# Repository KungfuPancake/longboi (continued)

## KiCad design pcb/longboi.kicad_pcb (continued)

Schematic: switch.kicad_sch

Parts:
C63: 100nF; C_0603_1608Metric
D15: LED; LED_0603_1608Metric
J23: JST-XH; JST_XH_B3B-XH-A_1x03_P2.50mm_Vertical
R29: 100k; R_0603_1608Metric
R30: 100; R_0603_1608Metric
R79: 3.3k; R_0603_1608Metric

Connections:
+5V: D15.2 (A), J23.3, R29.1; also elsewhere on the board
/Endstops/Switch 16/SW: R30.2, R79.1; also elsewhere on the board
GND: C63.2, J23.2; also elsewhere on the board
unnamed: D15.1 (K), R79.2
unnamed: C63.1, J23.1, R29.2, R30.1

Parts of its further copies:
C64, C65, C66, C67, C68, C69, C70, C71, C72, C73, C74, C75, C76, C77, C78: 100nF; C_0603_1608Metric
D16, D17, D18, D19, D20, D21, D22, D23, D24, D25, D26, D27, D28, D29, D30: LED; LED_0603_1608Metric
J24, J25, J26, J27, J28, J29, J30, J31, J32, J33, J34, J35, J36, J37, J38: JST-XH; JST_XH_B3B-XH-A_1x03_P2.50mm_Vertical
R31, R33, R35, R37, R39, R41, R43, R45, R47, R49, R51, R53, R55, R57, R59: 100k; R_0603_1608Metric
R32, R34, R36, R38, R40, R42, R44, R46, R48, R50, R52, R54, R56, R58, R60: 100; R_0603_1608Metric
R80, R81, R82, R83, R84, R85, R86, R87, R88, R89, R90, R91, R92, R93, R94: 3.3k; R_0603_1608Metric

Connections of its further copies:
+5V: D16.2 (A), D17.2 (A), D18.2 (A), D19.2 (A), D20.2 (A), D21.2 (A), D22.2 (A), D23.2 (A), D24.2 (A), D25.2 (A), D26.2 (A), D27.2 (A), D28.2 (A), D29.2 (A), D30.2 (A), J24.3, J25.3, J26.3, J27.3, J28.3, J29.3, J30.3, J31.3, J32.3, J33.3, J34.3, J35.3, J36.3, J37.3, J38.3, R31.1, R33.1, R35.1, R37.1, R39.1, R41.1, R43.1, R45.1, R47.1, R49.1, R51.1, R53.1, R55.1, R57.1, R59.1; also elsewhere on the board
/Endstops/Switch 1/SW: R60.2, R94.1; also elsewhere on the board
/Endstops/Switch 2/SW: R56.2, R92.1; also elsewhere on the board
/Endstops/Switch 3/SW: R48.2, R88.1; also elsewhere on the board
/Endstops/Switch 4/SW: R52.2, R90.1; also elsewhere on the board
/Endstops/Switch 5/SW: R44.2, R86.1; also elsewhere on the board
/Endstops/Switch 6/SW: R40.2, R84.1; also elsewhere on the board
/Endstops/Switch 7/SW: R36.2, R82.1; also elsewhere on the board
/Endstops/Switch 8/SW: R32.2, R80.1; also elsewhere on the board
/Endstops/Switch 9/SW: R58.2, R93.1; also elsewhere on the board
/Endstops/Switch 10/SW: R54.2, R91.1; also elsewhere on the board
/Endstops/Switch 11/SW: R50.2, R89.1; also elsewhere on the board
/Endstops/Switch 12/SW: R46.2, R87.1; also elsewhere on the board
/Endstops/Switch 13/SW: R42.2, R85.1; also elsewhere on the board
/Endstops/Switch 14/SW: R38.2, R83.1; also elsewhere on the board
/Endstops/Switch 15/SW: R34.2, R81.1; also elsewhere on the board
GND: C64.2, C65.2, C66.2, C67.2, C68.2, C69.2, C70.2, C71.2, C72.2, C73.2, C74.2, C75.2, C76.2, C77.2, C78.2, J24.2, J25.2, J26.2, J27.2, J28.2, J29.2, J30.2, J31.2, J32.2, J33.2, J34.2, J35.2, J36.2, J37.2, J38.2; also elsewhere on the board
unnamed: D16.1 (K), R80.2
unnamed: D17.1 (K), R81.2
unnamed: D18.1 (K), R82.2
unnamed: D19.1 (K), R83.2
unnamed: D20.1 (K), R84.2
unnamed: D21.1 (K), R85.2
unnamed: D22.1 (K), R86.2
unnamed: D23.1 (K), R87.2
unnamed: D24.1 (K), R88.2
unnamed: D25.1 (K), R89.2
unnamed: D26.1 (K), R90.2
unnamed: D27.1 (K), R91.2
unnamed: D28.1 (K), R92.2
unnamed: D29.1 (K), R93.2
unnamed: D30.1 (K), R94.2
unnamed: C64.1, J24.1, R31.2, R32.1
unnamed: C65.1, J25.1, R33.2, R34.1
unnamed: C66.1, J26.1, R35.2, R36.1
unnamed: C67.1, J27.1, R37.2, R38.1
unnamed: C68.1, J28.1, R39.2, R40.1
unnamed: C69.1, J29.1, R41.2, R42.1
unnamed: C70.1, J30.1, R43.2, R44.1
unnamed: C71.1, J31.1, R45.2, R46.1
unnamed: C72.1, J32.1, R47.2, R48.1
unnamed: C73.1, J33.1, R49.2, R50.1
unnamed: C74.1, J34.1, R51.2, R52.1
unnamed: C75.1, J35.1, R53.2, R54.1
unnamed: C76.1, J36.1, R55.2, R56.1
unnamed: C77.1, J37.1, R57.2, R58.1
unnamed: C78.1, J38.1, R59.2, R60.1

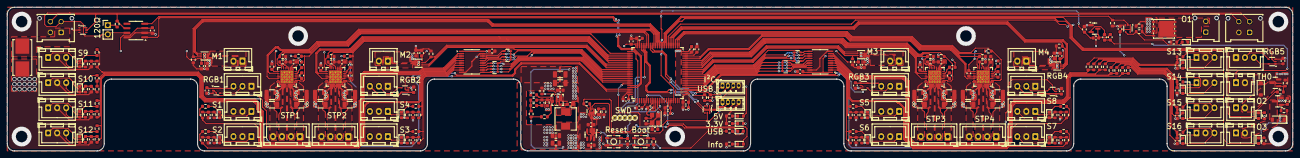
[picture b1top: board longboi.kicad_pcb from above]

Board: 4 copper layers, 358.0 x 40.0 mm, 288 parts (0 on the bottom side), 213 nets.

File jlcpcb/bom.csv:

Designator,Footprint,Quantity,Value,LCSC Part #
"C1, C4, C57, C59",0603,4,10uF,C19702
"C10, C18, C24, C30, C36, C8",0603,6,2.2uF,C23630
"C11, C12, C13, C14, C15, C17, C2, C23, C29, C35, C48, C49, C5, C50, C51, C52, C55, C56, C62, C63, C64, C65, C66, C67, C68, C69, C7, C70, C71, C72, C73, C74, C75, C76, C77, C78, C79, C80, C82, C9",0603,40,100nF,C14663
"C16, C22, C28, C34",0603,4,22nF,C21122
"C19, C25, C31, C37, C40, C41, C42, C43, C44, C45, C46, C47",0603,12,1uF,C15849
"C20, C21, C26, C27, C32, C33, C38, C39",1210,8,47uF,C6120020
"C3, C6",0603,2,12pF,C1644
"C53, C54",1206,2,10uF,C13585
C58,0603,1,100pF,C14665
"C60, C61",0805,2,22uF,C602037
D1,0603,1,Blue,C965807
"D10, D7",D_SOD-123,2,1N4007,C2902912
"D15, D16, D17, D18, D19, D20, D21, D22, D23, D24, D25, D26, D27, D28, D29, D30",0603,16,Yellow,C72038
"D2, D3, D4",0603,3,Green,C2994781
D32,SOT-23,1,BAV99,C2500
"D5, D6, D9",0603,3,Red,C965799
F1,Fuseholder_Littelfuse_Nano2_154x,1,4A,C108518
"J10, J7, J8, J9",JST_XH_B4B-XH-A_1x04_P2.50mm_Vertical,4,Conn_01x04_Pin,C566013
"J11, J12, J13, J14, J41, J44, J50",JST_XH_B2B-XH-A_1x02_P2.50mm_Vertical,7,Conn_01x02_Pin,C378939
"J15, J16, J17, J18, J23, J24, J25, J26, J27, J28, J29, J30, J31, J32, J33, J34, J35, J36, J37, J38, J40",JST_XH_B3B-XH-A_1x03_P2.50mm_Vertical,21,Conn_01x03_Pin,C565985
J19,PinHeader_1x02_P2.54mm_Vertical,1,Conn_01x02_Pin,C492401
"J20, J21",Molex_Micro-Fit_3.0_43045-0412_2x02_P3.00mm_Vertical,2,MX3.0,C277721
J39,Molex_Micro-Fit_3.0_43045-0212_2x01_P3.00mm_Vertical,1,Conn_01x02_Pin,C293362
"J42, J6",JST_ZH_B4B-ZR_1x04_P1.50mm_Vertical,2,JST-ZH,C157997
L1,L_Chilisin_BMRA00050530,1,L_Ferrite,C7187309
Q1,DFN-8_L5.9-W5.2-P1.27-LS6.2-BL,1,HY1904C2,C358116
"Q2, Q4",SOT-23,2,IRLML0030,C67272
"R1, R24, R64, R70",0603,4,2.7k,C13167
"R10, R11, R4, R5, R6, R7, R8, R9",1206,8,110m,C2934288
"R100, R101, R102, R103, R104, R105, R106, R107, R13, R16, R17, R28, R29, R31, R33, R35, R37, R39, R41, R43, R45, R47, R49, R51, R53, R55, R57, R59, R95, R96, R97, R98, R99",0603,33,100k,C14675
"R108, R109",0603,2,2.37k,C705759
R110,0603,1,4.7k,C99782
R12,0603,1,120,C22787
R14,0603,1,56k,C23206
R15,0603,1,0,C95177
"R18, R25, R61, R79, R80, R81, R82, R83, R84, R85, R86, R87, R88, R89, R90, R91, R92, R93, R94",0603,19,3.3k,C22978
R19,0603,1,20k,C2907011
"R2, R3",0603,2,15k,C22809
"R20, R23, R26, R27, R63, R66, R67, R68, R72",0603,9,10k,C98220
R21,0603,1,49.9,C114625
R22,0603,1,73.2k,C14890
"R30, R32, R34, R36, R38, R40, R42, R44, R46, R48, R50, R52, R54, R56, R58, R60, R62, R65, R71",0603,19,100,C105588
"RN1, RN2, RN3, RN4",R_Array_Convex_4x0603,4,10k,C29718
"SW1, SW2",SW-SMD_4P-L3.4-W3.4-P2.00-LS4.0_TS3315A160GF,2,SW_SPST,C557593
U1,LQFP-100_14x14mm_P0.5mm,1,STM32H723VGTx,C730142
"U10, U11, U8, U9",WSON-8-1EP_2x2mm_P0.5mm_EP0.9x1.6mm,4,DRV8837,C39159
"U12, U13, U14, U15, U21, U22",SOT-353_SC-70-5,6,74LVC1G126,C7394032
U16,SOIC-8_3.9x4.9mm_P1.27mm,1,SN65HVD231,C129257
U17,SOT-583-8,1,TPS2116DRL,C3235557
U18,VQFN-HR-10_L3.0-W3.0_RPA,1,TPS56637RPAR,C841386
U19,SOT-23-5,1,ME6211C33M5,C82942
"U2, U3",TSSOP-20_4.4x6.5mm_P0.65mm,2,SN74LVC245APW,C7848
"U20, U23",SOT-363_SC-70-6,2,SMF05CT1G-ES,C5180312
"U4, U5, U6, U7",QFN-28-1EP_5x5mm_P0.5mm_EP3.75x3.75mm_ThermalVias,4,TMC2209-LA,C2150710
Y1,Crystal_SMD_3225-4Pin_3.2x2.5mm,1,25MHz,C9006

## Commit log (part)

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2025-06-17 Create LICENSE
2025-06-17 add cad add stl reorganize pcb design files
2025-06-17 add images
2025-06-17 ignore lock files add katapult/klipper reference config
2025-06-17 add klipper board alias cfg
2025-06-20 add pcb step file
2025-06-25 fixes #3: increased input/output capacitor values for ME6211C33M5
2025-06-25 fixes #2: changed resistor divider values
2025-06-25 fixes #8: changed led series resistor values
2025-06-29 update pcb
2025-08-30 fixes #9 fixes #4 fixes #13
2025-08-31 fixes #6
2025-09-02 fixes #15
2025-09-02 fixes #5
2025-09-02 fixes #10
2025-09-02 fixes #12
2025-09-02 fixes #14
2025-09-25 fixes #7
2025-10-23 specified some values and colors added lcsc part ids for all components
2025-11-03 fixes #16
2025-11-03 add high resolution pinout image
2025-11-03 add pinout diagram
2025-11-03 now, actually
2025-11-12 fix wrong lcsc id for crystal cover up swapped net for sw3 and sw4 by swapping in config
2025-11-12 refactor image material
2025-11-12 update gerber files
2025-11-12 more image stuff
2025-11-24 spacer reoriented for printing
2025-11-24 re-export cad + stl with correct orientation and unit
2025-12-18 refactored cad/stl structure added step and stl files for BTE mounting
2025-12-18 actually fixed crystal lcsc id
2025-12-31 fixed pinout diagram
2026-01-08 fixes #20 fixes #22 fixes #19
2026-01-09 fix tmc2209 position in placement file
2026-01-28 fixes #24
2026-01-29 get ready for production fixes #24 fixes #25
2026-01-29 add jlcpcb production files
